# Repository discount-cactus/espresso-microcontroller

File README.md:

# Espresso

The main goal of the project is to design the most simple, barebones microcontroller board possible and then compliment the board with supporting modules to ultimately achieve a modular microcontroller that can be configured for a multitude of projects that a generic microcontroller can be used for.

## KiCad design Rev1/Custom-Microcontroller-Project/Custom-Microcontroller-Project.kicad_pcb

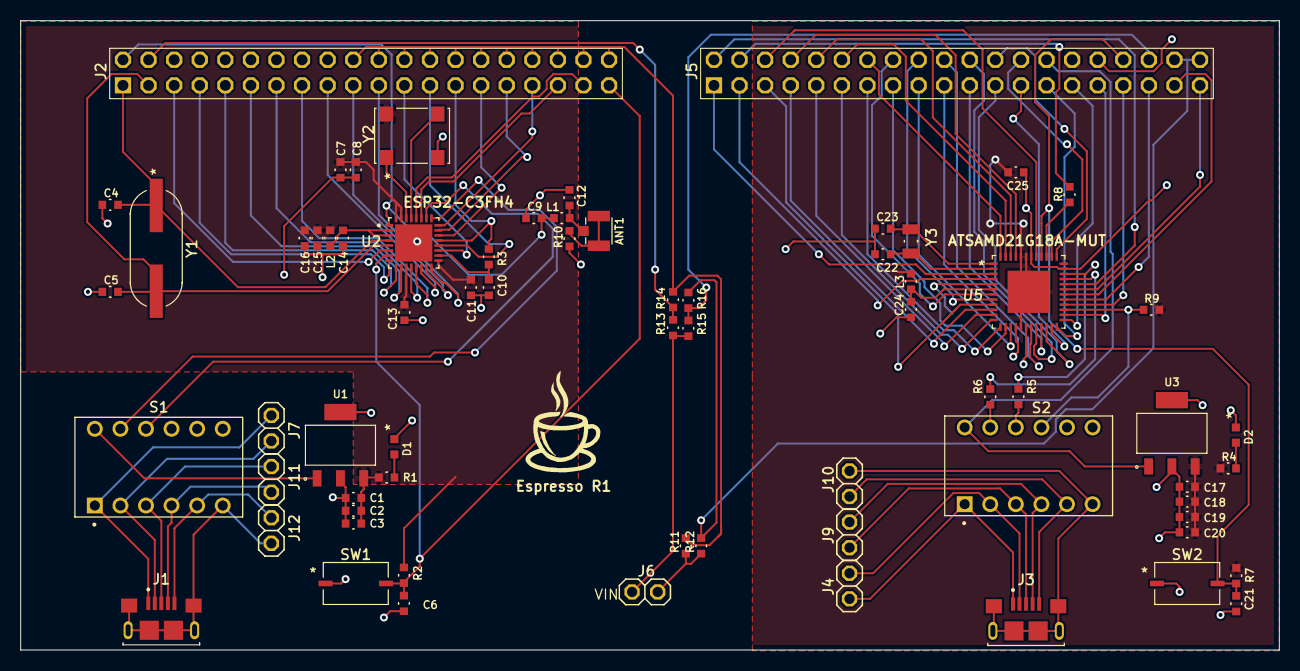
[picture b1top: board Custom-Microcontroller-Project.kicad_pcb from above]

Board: 2 copper layers, 125.0 x 62.5 mm, 69 parts (0 on the bottom side), 98 nets.

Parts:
ANT1: U.FL-R-SMT-1(10); HRS_U.FL-R-SMT-1(10)
C1, C6: 10uF; C_0603
C2, C8, C10, C17, C18: 1uF; C_0603
C3, C9, C11, C12, C13, C14, C15, C19, C21, C24, C25: 100nF; C_0603
C4, C5: 12pF; C_0603
C7, C16: 10nF; C_0603
C20: 4.7uF; C_0603
C22, C23: 20pF; C_0603
D1, D2: LTST-C191KGKT; LED_0603
J1, J3: AMPHENOL_10118193-0001LF; 10118193-0001LF
J2, J5: PPTC202LFBN-RC; 2X20
J4, J6, J7, J9, J10, J11, J12: 1X2
L1, L2, L3: 4.7nH; L_0603
R1, R4: 470ohm; R_0603
R2, R3, R7, R9: 10k; R_0603
R5, R6, R10, R11, R12: 0ohm; R_0603
R8: 10ohm; R_0603
R13, R14, R15, R16: 1Mohm; R_0603
S1, S2: DS01C-254-L-06BE; SW_DS01C-254-L-06BE
SW1, SW2: PTS636_SK25J_SMTR_LFS; PTS636 SK25J SMTR LFS
U1, U3: SOT-223_S_MCH; MIC5209-3.3YS
U2: ESP32-C3FH4; QFN50P500X500X90-33N
U5: QFN48_7X7MC_MCH; ATSAMD21G18A-MUT
Y1: HCM4916000000ABJT; Crystal_16MHz
Y2: ECS-3951M-400-BN-TR
Y3: ABS07-32.768KHZ-9-T; Crystal_32.768kHz

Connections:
/ESP32 Board/ANT: C9.2, J2.P$21 (21), L1.1, U2.1 (LNA_IN)
/ESP32 Board/ESP32_3V3: C1.2, C2.2, C3.2, C7.2, C8.2, C11.2, C13.2, C15.2, C16.2, L2.2, R1.2, R2.2, U1.3 (OUT), U2.11 (VDD3P3_RTC), U2.17 (VDD3P3_CPU), U2.31 (VDDA), U2.32 (VDDA), Y2.4 (VCC)
/ESP32 Board/ESP32_D+: S1.3B, U2.26 (GPIO19)
/ESP32 Board/ESP32_D-: S1.2B, U2.25 (GPIO18)
/ESP32 Board/ESP32_GND: C1.1, C2.1, C3.1, C4.1, C5.1, C6.1, C7.1, C8.1, C9.1, C10.1, C11.1, C12.1, C13.1, C14.1, C15.1, C16.1, D1.1, J2.P$23 (23), J2.P$24 (24), J2.P$25 (25), J2.P$26 (26), J2.P$27 (27), J2.P$28 (28), J2.P$29 (29), R10.1, S1.5B, S1.6B, SW1.1, U1.2 (GND), U1.4 (GND), U2.33 (GND), Y2.2 (GROUND)
/ESP32 Board/ESP32_VIN: S1.1B, U1.1 (IN)
/ESP32 Board/GPIO_0: C4.2, J2.P$1 (1), U2.4 (XTAL_32K_P), Y1.1
/ESP32 Board/GPIO_1: C5.2, J2.P$2 (2), U2.5 (XTAL_32K_N), Y1.2
/ESP32 Board/GPIO_2: J2.P$3 (3), U2.6 (GPIO2)
/ESP32 Board/GPIO_3: J2.P$4 (4), U2.8 (GPIO3)
/ESP32 Board/GPIO_4: J2.P$5 (5), U2.9 (MTMS)
/ESP32 Board/GPIO_5: J2.P$6 (6), U2.10 (MTDI)
/ESP32 Board/GPIO_6: J2.P$7 (7), U2.12 (MTCK)
/ESP32 Board/GPIO_7: J2.P$8 (8), U2.13 (MTDO)
/ESP32 Board/GPIO_8: J2.P$9 (9), U2.14 (GPIO8)
/ESP32 Board/GPIO_9: J2.P$10 (10), U2.15 (GPIO9)
/ESP32 Board/GPIO_10: J2.P$11 (11), U2.16 (GPIO10)
/ESP32 Board/GPIO_11: J2.P$12 (12), U2.19 (SPIHD)
/ESP32 Board/GPIO_12: J2.P$13 (13), U2.20 (SPIWP)
/ESP32 Board/GPIO_13: J2.P$14 (14), R3.1, U2.21 (SPICS0)
/ESP32 Board/GPIO_14: J2.P$15 (15), U2.22 (SPICLK)
/ESP32 Board/GPIO_15: J2.P$16 (16), U2.23 (SPID)
/ESP32 Board/GPIO_16: J2.P$17 (17), U2.24 (SPIQ)
/ESP32 Board/GPIO_17: J2.P$18 (18), U2.27 (RX)
/ESP32 Board/GPIO_18: J2.P$19 (19), U2.28 (TX)
/ESP32 Board/RESET: C6.2, J2.P$20 (20), R2.1, SW1.2, U2.7 (CHIP_EN_(RESET))
/ESP32 Board/SPI_VDD: C10.2, R3.2, U2.18 (VDD_SPI)
/ESP32 Board/VIN_LVL: J2.P$22 (22), R13.1, R14.2
/ESP32 Board/V_GND: J2.P$30 (30), J2.P$31 (31), J2.P$32 (32), J2.P$33 (33), J2.P$34 (34), J2.P$35 (35), J2.P$36 (36), J2.P$37 (37), J2.P$38 (38), J2.P$39 (39), J2.P$40 (40), R11.2, R14.1
/GND: J6.2, R11.1, R12.1
/SAMD Board/GPIO_2: J5.P$1 (1), U5.3 (PA02/AIN0)
/SAMD Board/GPIO_3: J5.P$2 (2), U5.4 (PA03)
/SAMD Board/GPIO_4: J5.P$3 (3), U5.9 (PA04/AIN4)
/SAMD Board/GPIO_5: J5.P$4 (4), U5.10 (PA05/AIN5)
/SAMD Board/GPIO_6: J5.P$5 (5), U5.11 (PA06/AIN6)
/SAMD Board/GPIO_7: J5.P$6 (6), U5.12 (PA07/AAIN7)
/SAMD Board/GPIO_8: J5.P$7 (7), U5.13 (PA08/SDA)
/SAMD Board/GPIO_9: J5.P$8 (8), U5.14 (PA09/SCL)
/SAMD Board/GPIO_10: J5.P$9 (9), U5.15 (PA10)
/SAMD Board/GPIO_11: J5.P$10 (10), U5.16 (PA11)
/SAMD Board/GPIO_12: J5.P$11 (11), U5.21 (PA12/MOSI2)
/SAMD Board/GPIO_13: J5.P$12 (12), U5.22 (PA13/SCK2)
/SAMD Board/GPIO_14: J5.P$13 (13), U5.23 (PA14/NSS2)
/SAMD Board/GPIO_15: J5.P$14 (14), U5.24 (PA15/MISO2)
/SAMD Board/GPIO_16: J5.P$15 (15), U5.25 (PA16/MOSI1)
/SAMD Board/GPIO_17: J5.P$16 (16), U5.26 (PA17/SCK1)
/SAMD Board/GPIO_19: J5.P$17 (17), U5.28 (PA19/MISO1)
/SAMD Board/GPIO_20: J5.P$18 (18), U5.29 (PA20)
/SAMD Board/GPIO_21: J5.P$19 (19), U5.30 (PA21)
/SAMD Board/GPIO_22: J5.P$20 (20), U5.31 (PA22)
/SAMD Board/GPIO_23: J5.P$21 (21), U5.32 (PA23)
/SAMD Board/GPIO_27: J5.P$22 (22), R8.2
/SAMD Board/GPIO_28: J5.P$23 (23), U5.41 (PA28)
/SAMD Board/GPIO_30: J5.P$24 (24), U5.45 (PA30/SWCLK)
/SAMD Board/GPIO_31: J5.P$25 (25), U5.46 (PA31/SWDIO)
/SAMD Board/GPIO_32: J5.P$26 (26), U5.47 (PB02/AIN10)
/SAMD Board/GPIO_33: J5.P$27 (27), U5.48 (PB03/AIN11)
/SAMD Board/GPIO_34: J5.P$28 (28), U5.7 (PB08)
/SAMD Board/GPIO_35: J5.P$29 (29), U5.8 (PB09)
/SAMD Board/GPIO_36: J5.P$30 (30), U5.19 (PB10)
/SAMD Board/GPIO_37: J5.P$31 (31), U5.20 (PB11)
/SAMD Board/GPIO_38: J5.P$32 (32), U5.37 (PB22/TX)
/SAMD Board/GPIO_39: J5.P$33 (33), U5.38 (PB23/RX)
/SAMD Board/SAMD_3V3: C17.2, C18.2, C19.2, C20.2, C25.2, J5.P$35 (35), L3.2, R4.2, R7.2, R9.2, U3.3 (OUT), U5.17 (VDDIO), U5.36 (VDDIO), U5.43 (VDDCORE), U5.44 (VDDIN), U5.49 (EPAD)
/SAMD Board/SAMD_D+: R5.2, S2.3B
/SAMD Board/SAMD_D-: R6.2, S2.2B
/SAMD Board/SAMD_GND: C17.1, C18.1, C19.1, C20.1, C21.1, C22.1, C23.1, C24.1, C25.1, D2.1, J5.P$36 (36), S2.5B, S2.6B, SW2.1, U3.2 (GND), U3.4 (GND), U5.5 (GNDANA), U5.18 (GND), U5.35 (GND), U5.42 (GND)
/SAMD Board/SAMD_RESET: C21.2, J5.P$37 (37), R7.1, SW2.2, U5.40 (*RESET)
/SAMD Board/SAMD_USB_ID: R9.1, S2.4B, U5.27 (PA18)
/SAMD Board/SAMD_VIN: J5.P$34 (34), S2.1B, U3.1 (IN)
/SAMD Board/VIN_LVL: J5.P$38 (38), R15.1, R16.2
/SAMD Board/V_GND: J5.P$39 (39), J5.P$40 (40), R12.2, R16.1
/VIN: J6.1, R13.2, R15.2
unnamed: ANT1.1, ANT1.3, R10.2
unnamed: ANT1.2, C12.2, L1.2
unnamed: C14.2, L2.1, U2.2 (VDD3P3), U2.3 (VDD3P3)
unnamed: D1.2, R1.1
unnamed: D2.2, R4.1
unnamed: J1.3 (D+), J11.1, S1.3A
unnamed: J1.2 (D-), J7.2, S1.2A
unnamed: J1.5 (GND), J12.1, S1.5A
unnamed: J1.4 (ID), J11.2, S1.4A
unnamed: J1.S1 (SHIELD), J1.S2 (SHIELD), J1.S3 (SHIELD), J1.S4 (SHIELD), J1.S5 (SHIELD), J1.S6 (SHIELD), J12.2, S1.6A
unnamed: J1.1 (VUSB), J7.1, S1.1A
unnamed: J3.3 (D+), J9.1, S2.3A
unnamed: J3.2 (D-), J4.2, S2.2A
unnamed: J3.5 (GND), J10.1, S2.5A
unnamed: J3.4 (ID), J9.2, S2.4A
unnamed: J3.1 (VUSB), J4.1, S2.1A
unnamed: J3.S1 (SHIELD), J3.S2 (SHIELD), J3.S3 (SHIELD), J3.S4 (SHIELD), J3.S5 (SHIELD), J3.S6 (SHIELD), J10.2, S2.6A
unnamed: U2.29 (XTAL_N), Y2.3 (OUTPUT)
unnamed: U2.30 (XTAL_P), Y2.1 (TRI-STATE)
unnamed: C23.2, U5.1 (PA00/XIN32), Y3.2
unnamed: C22.2, U5.2 (PA01/XOUT32), Y3.1
unnamed: R6.1, U5.33 (PA24/USB_D-)
unnamed: R5.1, U5.34 (PA25/USB_D+)
unnamed: R8.1, U5.39 (PA27)
unnamed: C24.2, L3.1, U5.6 (VDDANA)

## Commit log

2023-04-08 Added Rev1 kicad project and fab files
